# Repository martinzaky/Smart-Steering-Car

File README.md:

# Smart-Steering-Car project
components : ArduinoUNO , L298N Driver , 2 ULTRAsonic sensors , Servo motor , two motors , two potentiometers , LCD Display

tinkercad linkk : https://www.tinkercad.com/things/lkNFYMO2Fw9-martinnn-final-steering-car?sharecode=eKNPkrG-7DpUVj-WDK0rt8aDHa1EXqgV8EGHZmQ-iPM

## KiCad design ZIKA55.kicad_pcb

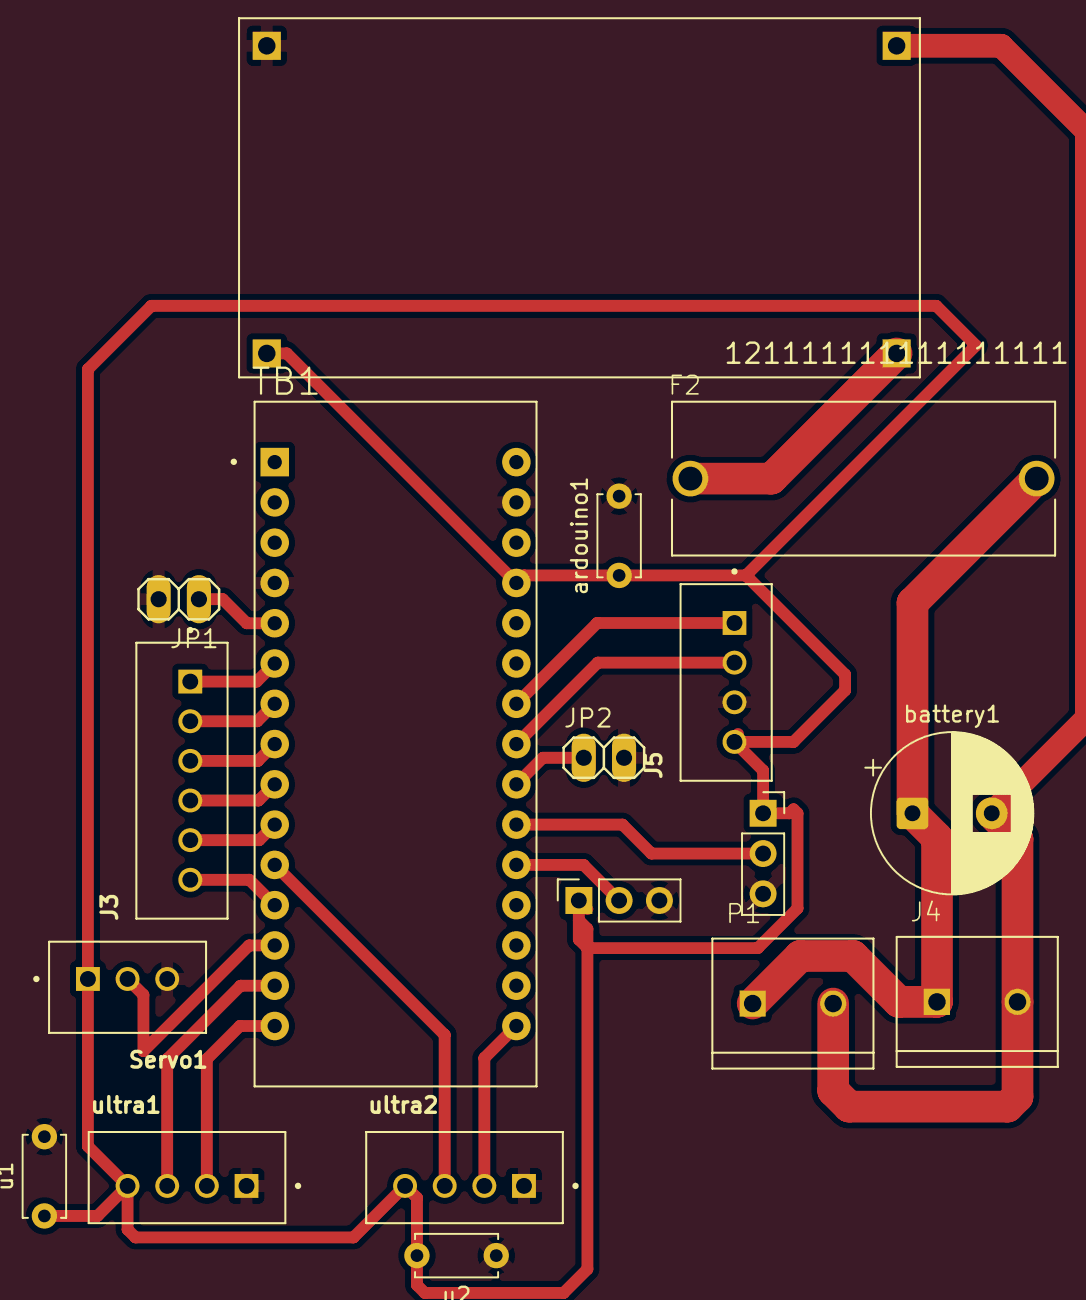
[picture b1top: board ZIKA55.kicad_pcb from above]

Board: 2 copper layers, 18 parts (0 on the bottom side), 23 nets.

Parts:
121111111111111111: LM2596
F2: FUSE_4527
J1, J2: Conn_01x03_Pin; PinSocket_1x03_P2.54mm_Vertical
J3: JST_B6B-XH-A(LF)(SN)
J4: TE_282837-2
J5: JST_B4B-XH-A(LF)(SN)
JP1, JP2: 1X02
P1: TE_282837-2
Servo1: JST_B3B-XH-A_(LF)(SN)
TB1: SHIELD_ARDUINO_NANO
ardouino1: C; C_Disc_D5.0mm_W2.5mm_P5.00mm
battery1: C; CP_Radial_D10.0mm_P5.00mm
u1, u2: C; C_Disc_D5.0mm_W2.5mm_P5.00mm
ultra1, ultra2: JST_B4B-XH-A(LF)(SN)

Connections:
+5V: 121111111111111111.OUT+, J1.1, J2.1, J5.4, Servo1.1, TB1.27 (+5V), ardouino1.1, u1.1, u2.2, ultra1.4, ultra2.4
+12V: F2.2, J4.1, P1.1, battery1.1
/<NO NET>: TB1.11 (D8), ultra2.3
/ECHO: TB1.14 (D11/MOSI), ultra1.3
/Servo: Servo1.2, TB1.13 (D10)
/TRG: TB1.15 (D12/MISO), ultra1.2
/TRG2: TB1.16 (D13/SCK), ultra2.2
/a4: J5.2, TB1.23 (A4)
/a5: J5.1, TB1.24 (A5)
/ang1: J1.2, TB1.20 (A1)
/ang2: J2.2, TB1.21 (A2)
/d1: J3.2, TB1.7 (D4)
/d2: J3.3, TB1.8 (D5)
/d3: J3.4, TB1.9 (D6)
/d4: J3.5, TB1.10 (D7)
/p1: J3.1, TB1.6 (D3)
/p2: J3.6, TB1.12 (D9)
/push: JP1.1, TB1.5 (D2)
/push 2: JP2.1, TB1.22 (A3)
GND: 121111111111111111.OUT-, J1.3, J2.3, J5.3, JP1.2, JP2.2, Servo1.3, TB1.4 (COM/GND), TB1.29 (COM/GND), ardouino1.2, u1.2, u2.1, ultra1.1, ultra2.1
GND1: 121111111111111111.IN-, J4.2, P1.2, battery1.2
unnamed: 121111111111111111.IN+, F2.1
unnamed: TB1.3 (RESET), TB1.28 (RESET)
